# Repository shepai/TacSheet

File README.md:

# TacSheet
PCB designs and demo test code for the TacSheet

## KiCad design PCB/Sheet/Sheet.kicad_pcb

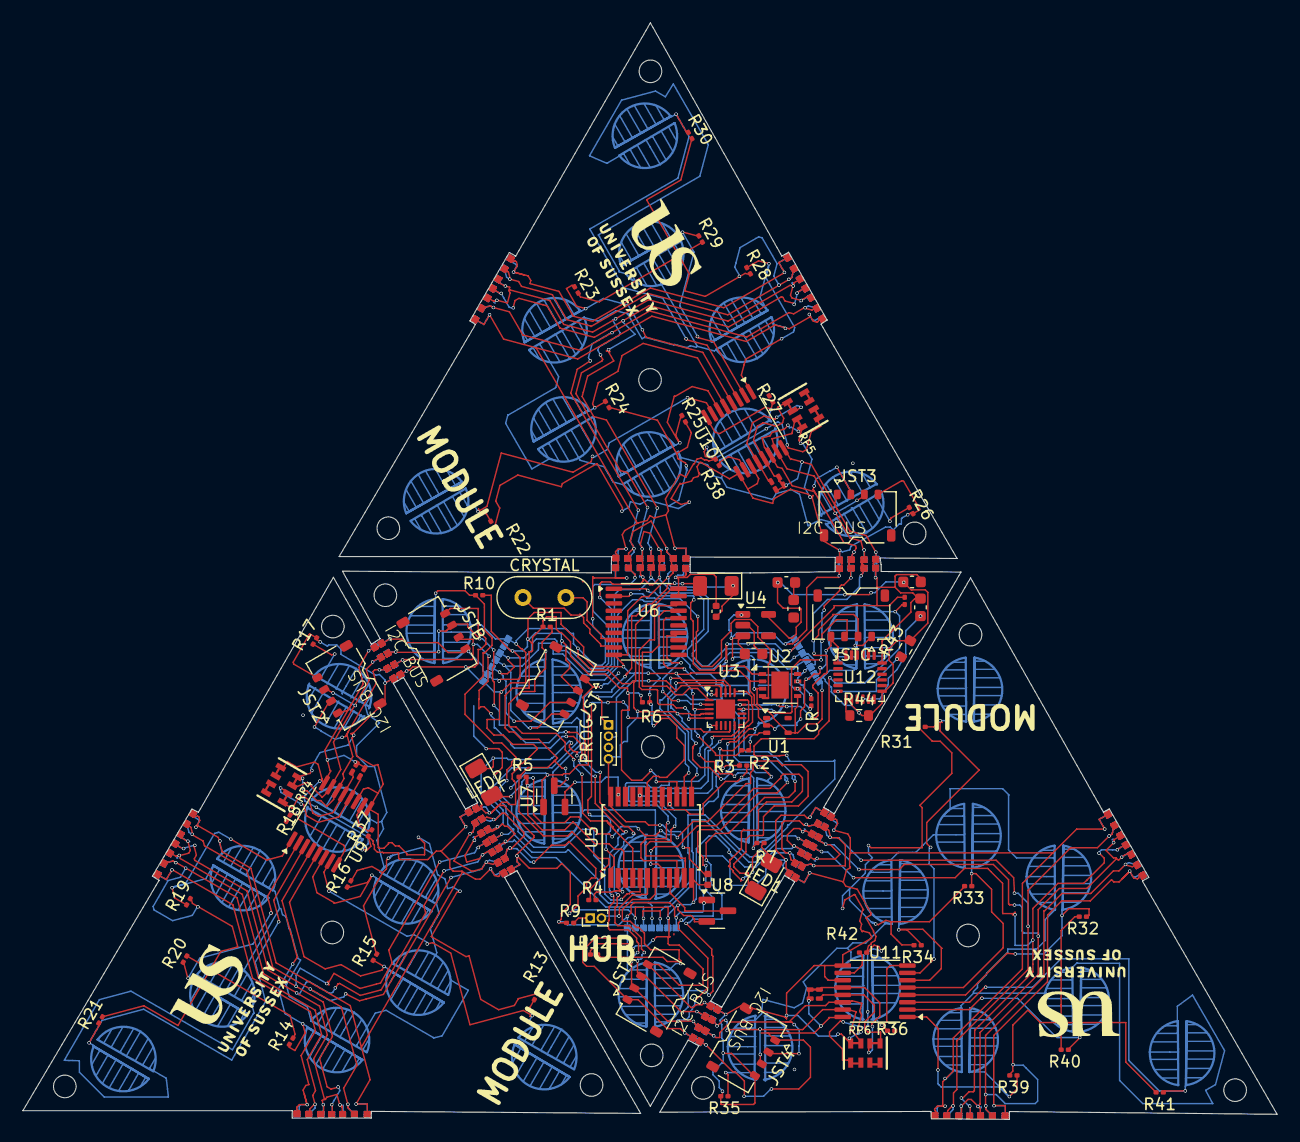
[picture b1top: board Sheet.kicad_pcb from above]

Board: 2 copper layers, 111.0 x 97.1 mm, 84 parts (0 on the bottom side), 46 nets.

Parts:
C1, C3: C; C_0402_1005Metric
C8: 4.7uF; C_0603_1608Metric
C10, C12, C13: 0.1uF; C_0603_1608Metric
C14: 220pF; C_0603_1608Metric
CR: 120; R_0201_0603Metric
CRYSTAL: Crystal_HC52-6mm_Vertical
JST, JST2, JST3, JST4: JST_ACH_BM04B-ACHSS-A-GAN-ETF_1x04-1MP_P1.20mm_Ve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; JST_ACH_BM04B-ACHSS-A-GAN-ETF_1x04-1MP_P1.20mm_Vertical
JSTA: JST_ACH_BM04B-ACHSS-A-GAN-ETF_1x04-1MP_P1.20mm_Ve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; JST_ACH_BM04B-ACHSS-A-GAN-ETF_1x04-1MP_P1.20mm_Vertical
JSTB: JST_ACH_BM04B-ACHSS-A-GAN-ETF_1x04-1MP_P1.20mm_Ve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; JST_ACH_BM04B-ACHSS-A-GAN-ETF_1x04-1MP_P1.20mm_Vertical
JSTC: JST_ACH_BM04B-ACHSS-A-GAN-ETF_1x04-1MP_P1.20mm_Ve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; JST_ACH_BM04B-ACHSS-A-GAN-ETF_1x04-1MP_P1.20mm_Vertical
LED1, LED2, LED3: LED_1206_3216Metric
P1, P1#2, P2, P3, P4, P5: C_0201_0603Metric_Pad0.64x0.40mm_HandSolder
PROG: PinHeader_1x04_P1.00mm_Vertical
R1, R2, R3, R4, R5, R6, R7, R10, R11, R12, R13, R14, R15, R16, R17, R18, R19, R20, R21, R22, R23, R24, R25, R26, R27, R28, R29, R30, R31, R32, R33, R34, R35, R36, R37, R38, R39, R40, R41, R42: R; R_0201_0603Metric
R9: R9; R_0201_0603Metric
R43, R44: 4.7k; R_0603_1608Metric
RP4, RP5, RP6: 10K Pack; RESPACK_4X0603
U1: MCP9700Ax-ELT; SOT-353_SC-70-5
U2: MCP2562-E-MF; DFN-8-1EP_3x3mm_P0.65mm_EP1.55x2.4mm
U3: ATtiny1616-M; VQFN-20-1EP_3x3mm_P0.4mm_EP1.7x1.7mm
U4: AP2112K-3.3; SOT-23-5
U5: CD74HC4067SM; SSOP-24_5.3x8.2mm_P0.65mm
U6: MCP2515-xST; TSSOP-20_4.4x6.5mm_P0.65mm
U7, U8: DRV5055A1xDBZxQ1; SOT-23
U9, U10, U11: ADS7830; TSSOP-16_4.4x5mm_P0.65mm
U12: MPU-6050; InvenSense_QFN-24_4x4mm_P0.5mm

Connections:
+3V3: C10.1, C12.1, R43.2, R44.2, U4.5 (VOUT), U12.8 (VLOGIC), U12.13 (VDD)
+5V: C8.1, U4.1 (VIN), U4.3 (EN)
/XCL: R44.1, U12.7 (AUX_CL)
/XDA: R43.1, U12.6 (AUX_DA)
GND: C8.2, C10.2, C12.2, C13.2, C14.2, U4.2 (GND), U12.1 (CLKIN), U12.11 (FSYNC), U12.18 (GND)
unnamed: U1.2 (GND), U3.3 (GND), U3.21 (GND)
unnamed: C1.1, C3.2, R1.1, R2.1, R3.1, R4.1, R5.1, R6.1, R10.1, R11.1, R12.1, R13.1, R14.1, R15.1, R16.1, R17.1, R18.1, R19.1, R21.1, R22.1, R23.1, R24.1, R25.1, R26.1, R27.1, R28.1, R30.1, R31.1, R32.1, R33.1, R34.1, R35.1, R36.1, R39.1, R41.1, U2.2 (VSS), U5.12 (GND), U5.15 (~E), U6.10 (VSS), U7.3 (GND), U8.3 (GND), U9.9 (GND), U9.11 (COM), U10.9 (GND), U10.11 (COM), U11.9 (GND), U11.11 (COM)
unnamed: C1.2, C3.1, R37.1, R38.1, R42.1, U1.4 (V_{DD}), U2.3 (VDD), U2.5 (Vio), U5.24 (VCC), U6.19 (~RESET), U6.20 (VDD), U7.1 (VCC), U8.1 (VCC), U9.16 (VDD), U10.16 (VDD), U11.16 (VDD)
unnamed: U1.3 (V_{OUT}), U5.20 (I11)
unnamed: U2.4 (RXD), U6.2 (RXCAN)
unnamed: U2.1 (TXD), U6.1 (TXCAN)
unnamed: U3.20 (PA1), U6.16 (SI)
unnamed: U3.1 (PA2), U6.17 (SO)
unnamed: U3.2 (PA3), U6.14 (SCK)
unnamed: U3.5 (PA4), U6.18 (~CS)
unnamed: R7.1, U3.6 (PA5)
unnamed: U3.9 (PB5), U5.1 (COM)
unnamed: U3.15 (PC0), U5.10 (S0)
unnamed: U3.16 (PC1), U5.11 (S1)
unnamed: U3.17 (PC2), U5.14 (S2)
unnamed: U3.18 (PC3), U5.13 (S3)
unnamed: U5.9 (I0), U8.2 (OUT)
unnamed: R12.2, U5.8 (I1)
unnamed: R11.2, U5.7 (I2)
unnamed: R10.2, U5.5 (I4)
unnamed: R1.2, U5.4 (I5)
unnamed: R5.2, U5.3 (I6)
unnamed: R4.2, U5.2 (I7)
unnamed: U5.23 (I8), U7.2 (OUT)
unnamed: R6.2, U5.19 (I12)
unnamed: R3.2, U5.17 (I14)
unnamed: R2.2, U5.16 (I15)
unnamed: R13.2, R22.2, R31.2, U9.1 (CH0), U10.1 (CH0), U11.1 (CH0)
unnamed: R14.2, R23.2, R32.2, U9.2 (CH1), U10.2 (CH1), U11.2 (CH1)
unnamed: R15.2, R24.2, R33.2, U9.3 (CH2), U10.3 (CH2), U11.3 (CH2)
unnamed: R16.2, R25.2, R34.2, U9.4 (CH3), U10.4 (CH3), U11.4 (CH3)
unnamed: R17.2, R26.2, R35.2, U9.5 (CH4), U10.5 (CH4), U11.5 (CH4)
unnamed: R18.2, R27.2, R36.2, U9.6 (CH5), U10.6 (CH5), U11.6 (CH5)
unnamed: R19.2, R28.2, R39.2, U9.7 (CH6), U10.7 (CH6), U11.7 (CH6)
unnamed: R20.2, R29.2, R40.2, U9.8 (CH7), U10.8 (CH7), U11.8 (CH7)
unnamed: R37.2, R38.2, R42.2, U9.10 (REFin/REFout), U10.10 (REFin/REFout), U11.10 (REFin/REFout)
unnamed: R21.2, R30.2, R41.2
unnamed: U3.14 (PB0), U9.14 (SCL), U10.14 (SCL), U11.14 (SCL)
unnamed: U3.13 (PB1), U9.15 (SDA), U10.15 (SDA), U11.15 (SDA)
unnamed: C14.1, U12.20 (CPOUT)
unnamed: C13.1, U12.10 (REGOUT)

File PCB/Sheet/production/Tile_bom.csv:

Designator,Footprint,Quantity,Value,LCSC Part #
"C1, C3",0402,2,C_0402_1005Metric,C2991468
"C1A, C2A, C3A",0402,3,C_0402_1005Metric_Pad0.74x0.62mm_HandSolder,C2991386
CR,0201,1,120,
CRYSTAL,Crystal_SMD_2012-2Pin_2.0x1.2mm,1,Crystal_SMD_2012-2Pin_2.0x1.2mm,
IC1,16LCSP,1,ADXL33X,
JST,JST_ACH_BM04B-ACHSS-A-GAN-ETF_1x04-1MP_P1.20mm_Vertical,1,JST_ACH_BM04B-ACHSS-A-GAN-ETF_1x04-1MP_P1.20mm_Vertical,C160404
"LED1, LED2, LED3",1206,3,LED_1206_3216Metric,C14641
PROG,PinHeader_1x04_P1.00mm_Vertical,1,PinHeader_1x04_P1.00mm_Vertical,
"R1, R10, R11, R12, R2, R3, R4, R5, R6, R7",0201,10,R_0201_0603Metric,C2129186
U1,SOT-353_SC-70-5,1,MCP9700Ax-ELT,C97546
U2,DFN-8-1EP_3x3mm_P0.65mm_EP1.55x2.4mm,1,MCP2562-E-MF,C53609
U3,VQFN-20-1EP_3x3mm_P0.4mm_EP1.7x1.7mm,1,ATtiny1616-M,C507118
U5,SSOP-24_5.3x8.2mm_P0.65mm,1,CD74HC4067SM,C98457
U6,TSSOP-20_4.4x6.5mm_P0.65mm,1,MCP2515-xST,C15193
"U7, U8",SOT-23,2,DRV5055A1xDBZxQ1,C962987
